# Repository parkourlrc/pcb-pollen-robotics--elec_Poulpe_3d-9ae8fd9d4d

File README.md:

# "Poulpe_3d" Electronic Board

"Poulpe_3d" is build from "Poulpe" as it aims on driving Orbita 3 Dofs. It is paireds with boards "Ventouse_3d" that drive 3 small BLDC Motors.

## Basically
 - Primarly designed for Reachy 2 gamma.
 - Powered in 24V.
 - Designed with KiCAD 7.

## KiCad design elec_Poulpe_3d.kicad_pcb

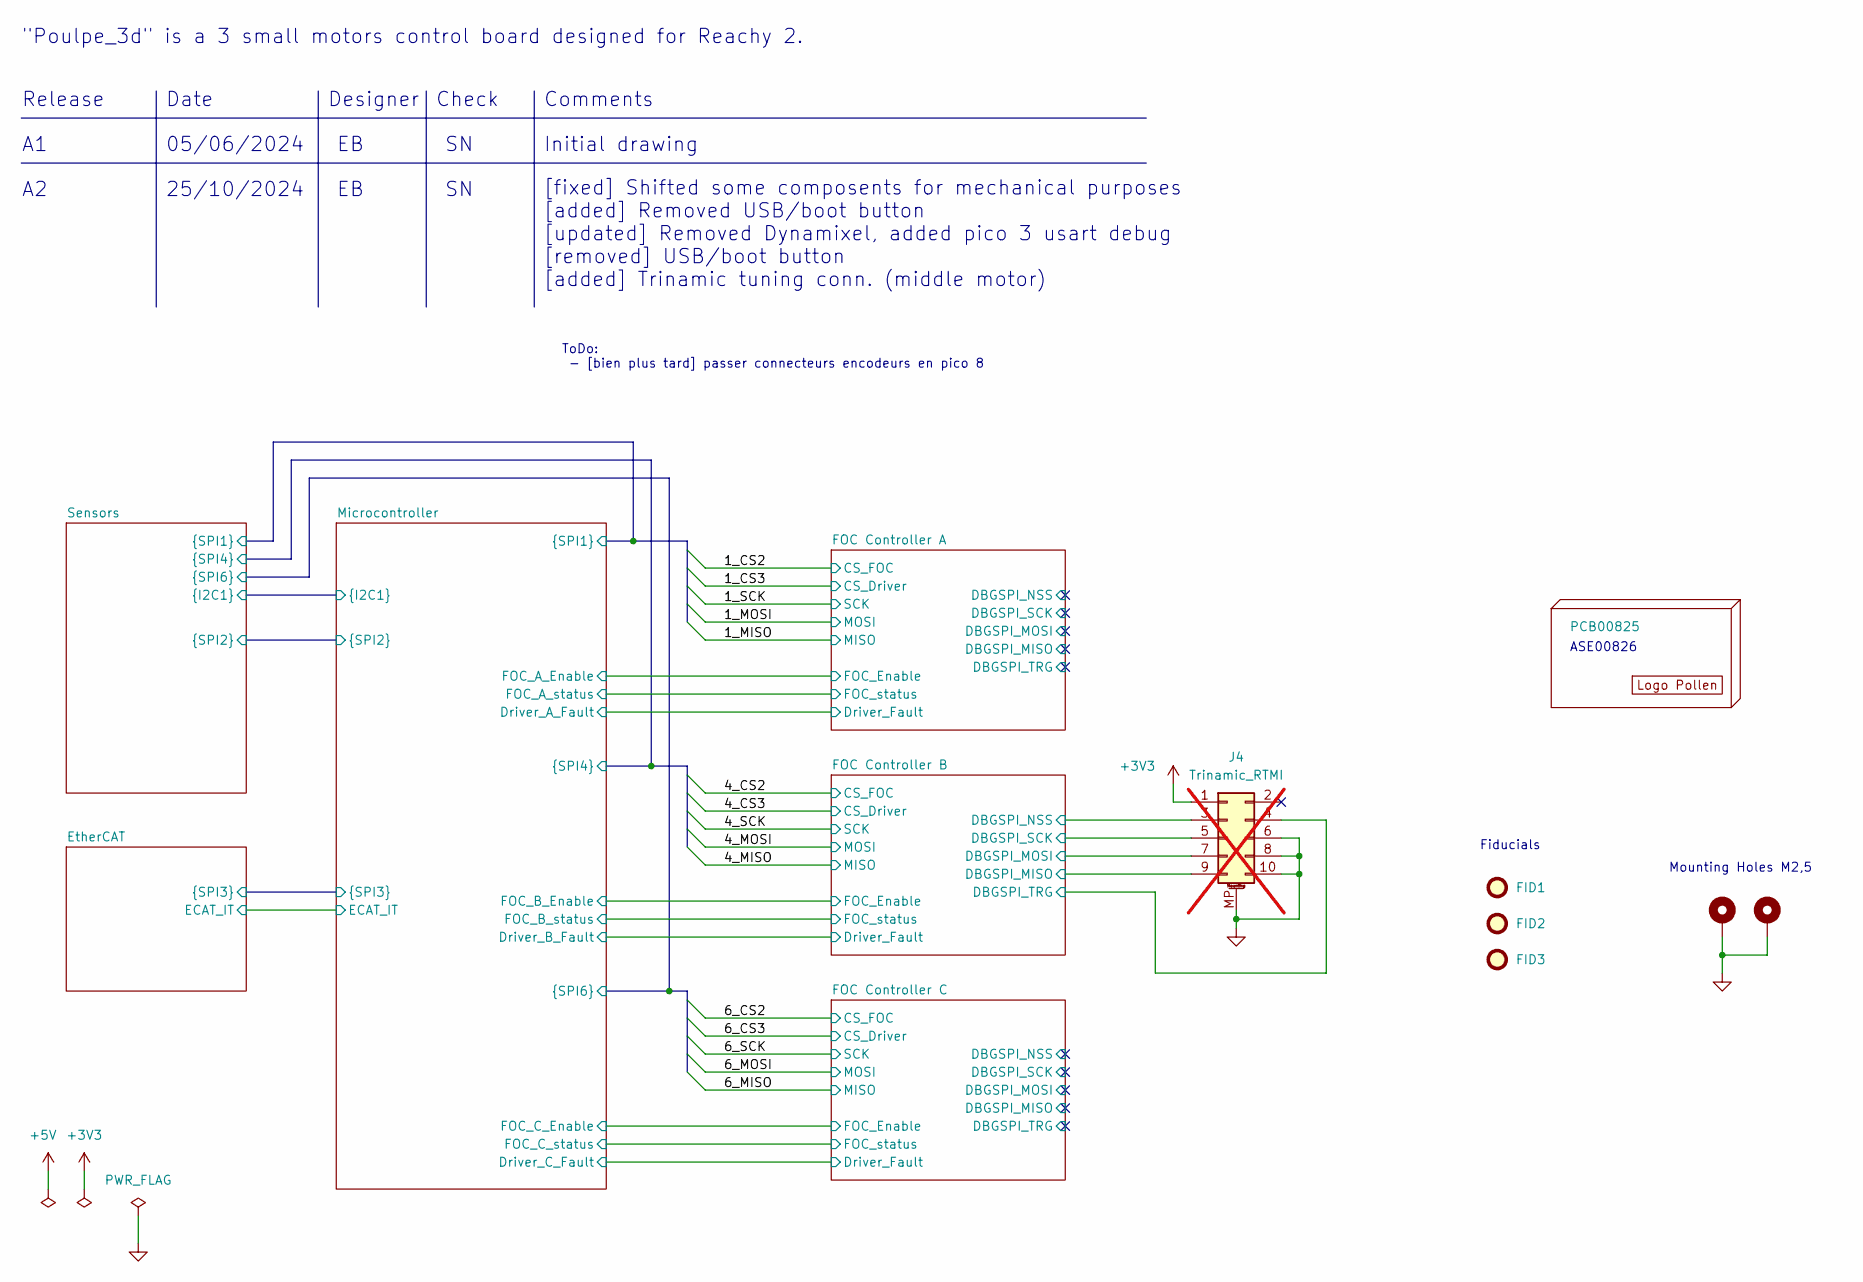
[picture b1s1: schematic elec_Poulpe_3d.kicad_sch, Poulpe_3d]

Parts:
FID1, FID2, FID3: DNP Fiducial; Fiducial_1mm_Mask2mm
H1: PCB00825
H2: DNP Logo Pollen 2021; Logo_Pollen_2021_sq
H3, H4: MountingHole_Pad; MountingHole_2.7mm_M2.5_ISO14580_Pad_TopBottom
J4: Trinamic_RTMI; DF20EF-10DP-1V (52); not fitted

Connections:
/FOC Controller B/DBGSPI_MISO: J4.9; also elsewhere on the board
/FOC Controller B/DBGSPI_MOSI: J4.7; also elsewhere on the board
/FOC Controller B/DBGSPI_NSS: J4.3; also elsewhere on the board
/FOC Controller B/DBGSPI_SCK: J4.5; also elsewhere on the board
/FOC Controller B/DBGSPI_TRG: J4.4; also elsewhere on the board

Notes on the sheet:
Mounting Holes M2,5
Date
Check
Release
Fiducials
ASE00826
Initial drawing
"Poulpe_3d" is a 3 small motors control board designed for Reachy 2.
Designer
25/10/2024
[fixed] Shifted some composents for mechanical purposes [added] Removed USB/boot button [updated] Removed Dynamixel, added pico 3 usart debug [removed] USB/boot button [added] Trinamic tuning conn. (middle motor)
Comments
ToDo: - [bien plus tard] passer connecteurs encodeurs en pico 8
05/06/2024

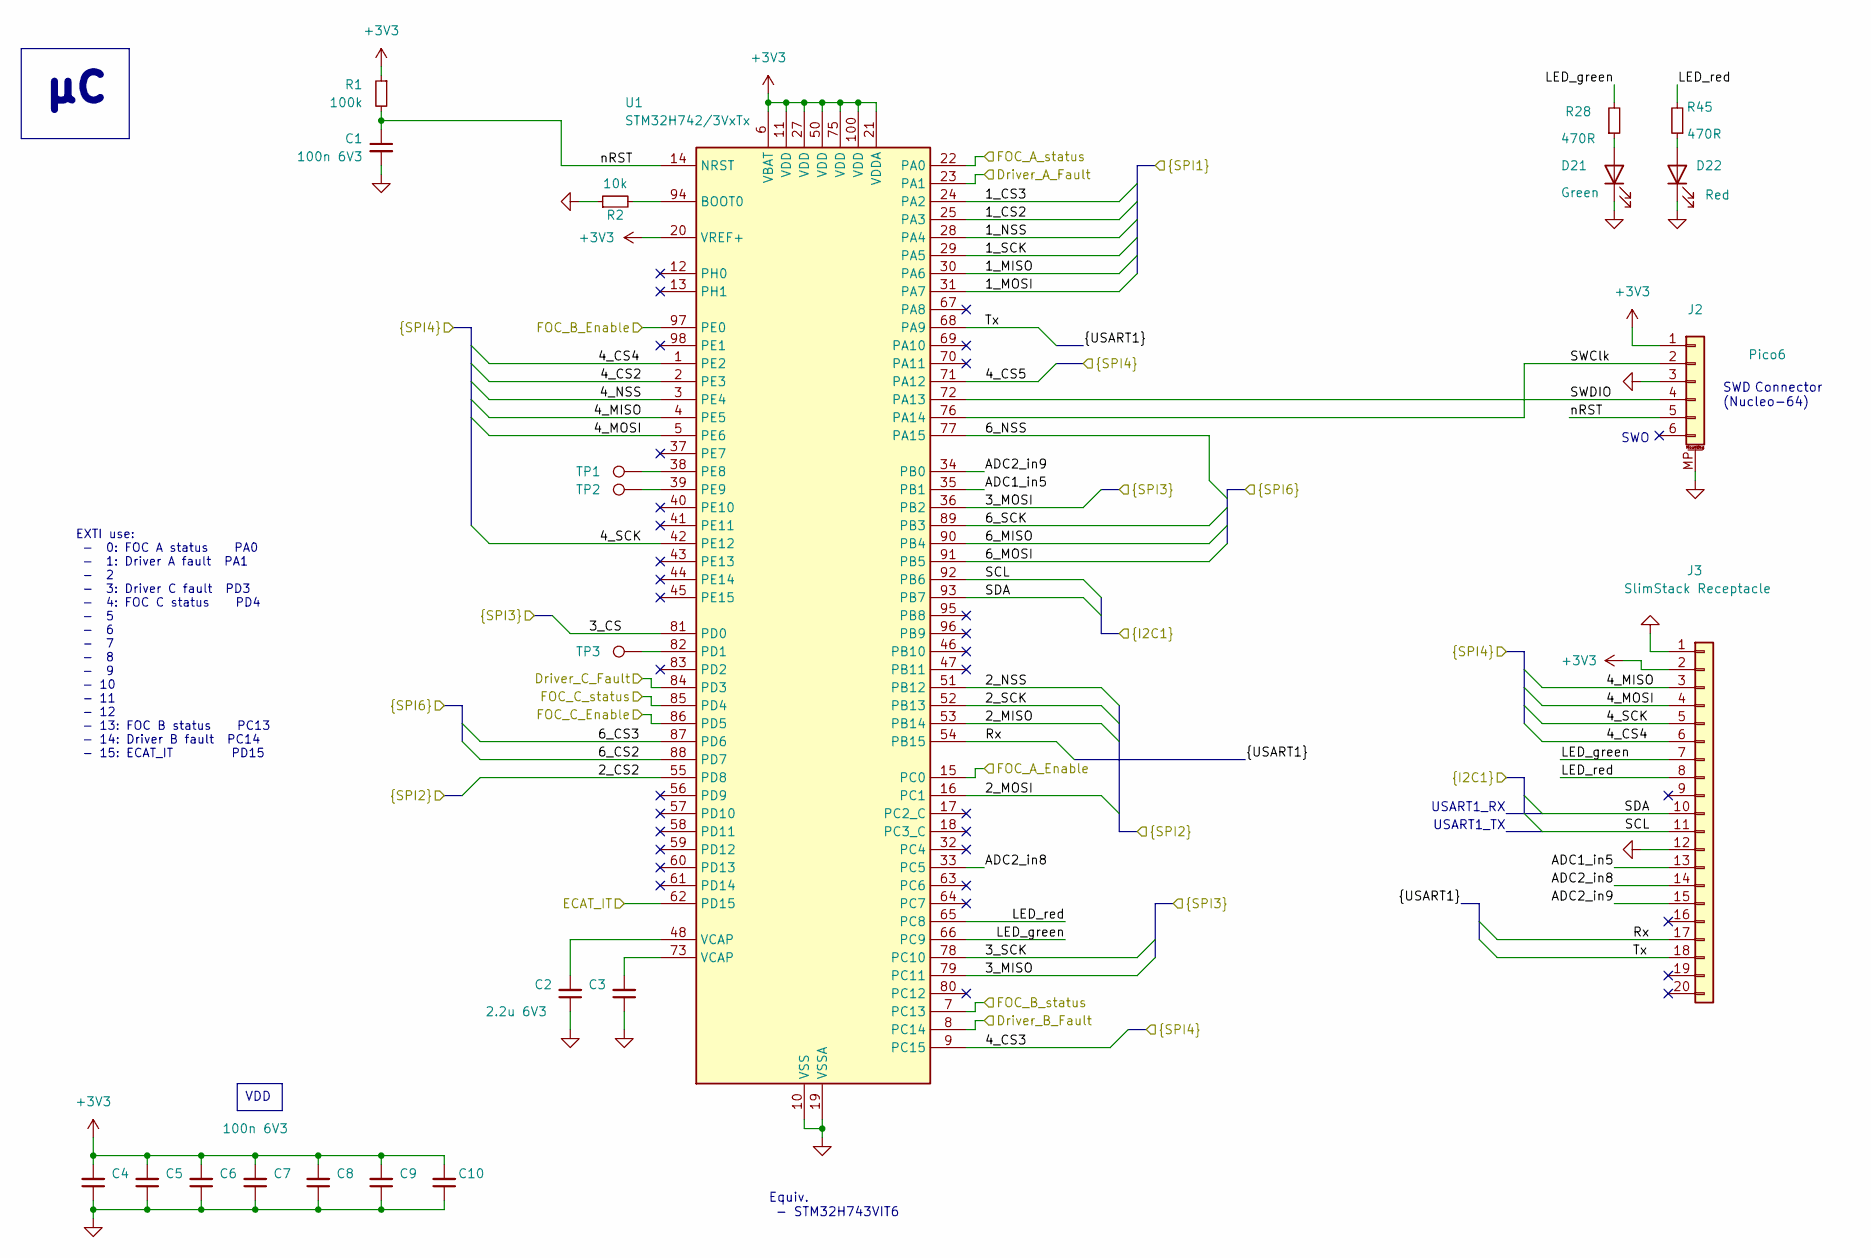
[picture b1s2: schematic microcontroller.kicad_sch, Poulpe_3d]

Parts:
C1, C4, C5, C6, C7, C8, C9, C10: 100n 6V3; C_0402_1005Metric
C2, C3: 2.2u 6V3; C_0603_1608Metric
D21: Green; LED_0603_1608Metric
D22: Red; LED_0603_1608Metric
J2: Pico6; Molex_PicoBlade_53261-0671_1x06-1MP_P1.25mm_Horizontal
J3: SlimStack Receptacle; Molex_SlimStack_529910208
R1: 100k; R_0402_1005Metric
R2: 10k; R_0402_1005Metric
R28, R45: 470R; R_0402_1005Metric
TP1, TP2, TP3: DNP - TestPoint; TestPoint_THTPad_D1.0mm_Drill0.4mm
U1: STM32H742/3VxTx; LQFP-100_14x14mm_P0.5mm

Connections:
/EtherCAT/3_CS: U1.81 (PD0); also elsewhere on the board
/EtherCAT/3_MISO: U1.79 (PC11); also elsewhere on the board
/EtherCAT/3_MOSI: U1.36 (PB2); also elsewhere on the board
/EtherCAT/3_SCK: U1.78 (PC10); also elsewhere on the board
/EtherCAT/ECAT_IT: U1.62 (PD15); also elsewhere on the board
/FOC Controller A/Driver_Fault: U1.23 (PA1); also elsewhere on the board
/FOC Controller A/FOC_Enable: U1.15 (PC0); also elsewhere on the board
/FOC Controller A/FOC_status: U1.22 (PA0); also elsewhere on the board
/FOC Controller B/Driver_Fault: U1.8 (PC14); also elsewhere on the board
/FOC Controller B/FOC_Enable: U1.97 (PE0); also elsewhere on the board
/FOC Controller B/FOC_status: U1.7 (PC13); also elsewhere on the board
/FOC Controller C/Driver_Fault: U1.84 (PD3); also elsewhere on the board
/FOC Controller C/FOC_Enable: U1.86 (PD5); also elsewhere on the board
/FOC Controller C/FOC_status: U1.85 (PD4); also elsewhere on the board
/Microcontroller/1_CS2: U1.25 (PA3); also elsewhere on the board
/Microcontroller/1_CS3: U1.24 (PA2); also elsewhere on the board
/Microcontroller/1_MISO: U1.30 (PA6); also elsewhere on the board
/Microcontroller/1_MOSI: U1.31 (PA7); also elsewhere on the board
/Microcontroller/1_NSS: U1.28 (PA4); also elsewhere on the board
/Microcontroller/1_SCK: U1.29 (PA5); also elsewhere on the board
/Microcontroller/2_CS2: U1.55 (PD8); also elsewhere on the board
/Microcontroller/2_MISO: U1.53 (PB14); also elsewhere on the board
/Microcontroller/2_MOSI: U1.16 (PC1); also elsewhere on the board
/Microcontroller/2_NSS: U1.51 (PB12); also elsewhere on the board
/Microcontroller/2_SCK: U1.52 (PB13); also elsewhere on the board
/Microcontroller/4_CS2: U1.2 (PE3); also elsewhere on the board
/Microcontroller/4_CS3: U1.9 (PC15); also elsewhere on the board
/Microcontroller/4_CS4: J3.6, U1.1 (PE2)
/Microcontroller/4_CS5: U1.71 (PA12); also elsewhere on the board
/Microcontroller/4_MISO: J3.3, U1.4 (PE5); also elsewhere on the board
/Microcontroller/4_MOSI: J3.4, U1.5 (PE6); also elsewhere on the board
/Microcontroller/4_NSS: U1.3 (PE4); also elsewhere on the board
/Microcontroller/4_SCK: J3.5, U1.42 (PE12); also elsewhere on the board
/Microcontroller/6_CS2: U1.88 (PD7); also elsewhere on the board
/Microcontroller/6_CS3: U1.87 (PD6); also elsewhere on the board
/Microcontroller/6_MISO: U1.90 (PB4); also elsewhere on the board
/Microcontroller/6_MOSI: U1.91 (PB5); also elsewhere on the board
/Microcontroller/6_NSS: U1.77 (PA15); also elsewhere on the board
/Microcontroller/6_SCK: U1.89 (PB3); also elsewhere on the board
/Microcontroller/ADC1_in5: J3.13, U1.35 (PB1)
/Microcontroller/ADC2_in8: J3.14, U1.33 (PC5)
/Microcontroller/ADC2_in9: J3.15, U1.34 (PB0)
/Microcontroller/LED_green: J3.7, R28.2, U1.66 (PC9)
/Microcontroller/LED_red: J3.8, R45.2, U1.65 (PC8)
/Microcontroller/Rx: J3.17, U1.54 (PB15)
/Microcontroller/SCL: J3.11, U1.92 (PB6); also elsewhere on the board
/Microcontroller/SDA: J3.10, U1.93 (PB7); also elsewhere on the board
/Microcontroller/SWClk: J2.2, U1.76 (PA14)
/Microcontroller/SWDIO: J2.4, U1.72 (PA13)
/Microcontroller/Tx: J3.18, U1.68 (PA9)
/Microcontroller/nRST: C1.1, J2.5, R1.2, U1.14 (NRST)
unnamed: C2.2, U1.48 (VCAP)
unnamed: C3.2, U1.73 (VCAP)
unnamed: D21.2 (A), R28.1
unnamed: D22.2 (A), R45.1
unnamed: R2.2, U1.94 (BOOT0)
unnamed: TP3.1, U1.82 (PD1)
unnamed: TP1.1, U1.38 (PE8)
unnamed: TP2.1, U1.39 (PE9)

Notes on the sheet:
VDD
SWO
USART1_RX
USART1_TX
EXTI use: - 0: FOC A status PA0 - 1: Driver A fault PA1 - 2 - 3: Driver C fault PD3 - 4: FOC C status PD4 - 5 - 6 - 7 - 8 - 9 - 10 - 11 - 12 - 13: FOC B status PC13 - 14: Driver B fault PC14 - 15: ECAT_IT PD15
Equiv. - STM32H743VIT6
SWD Connector (Nucleo-64)

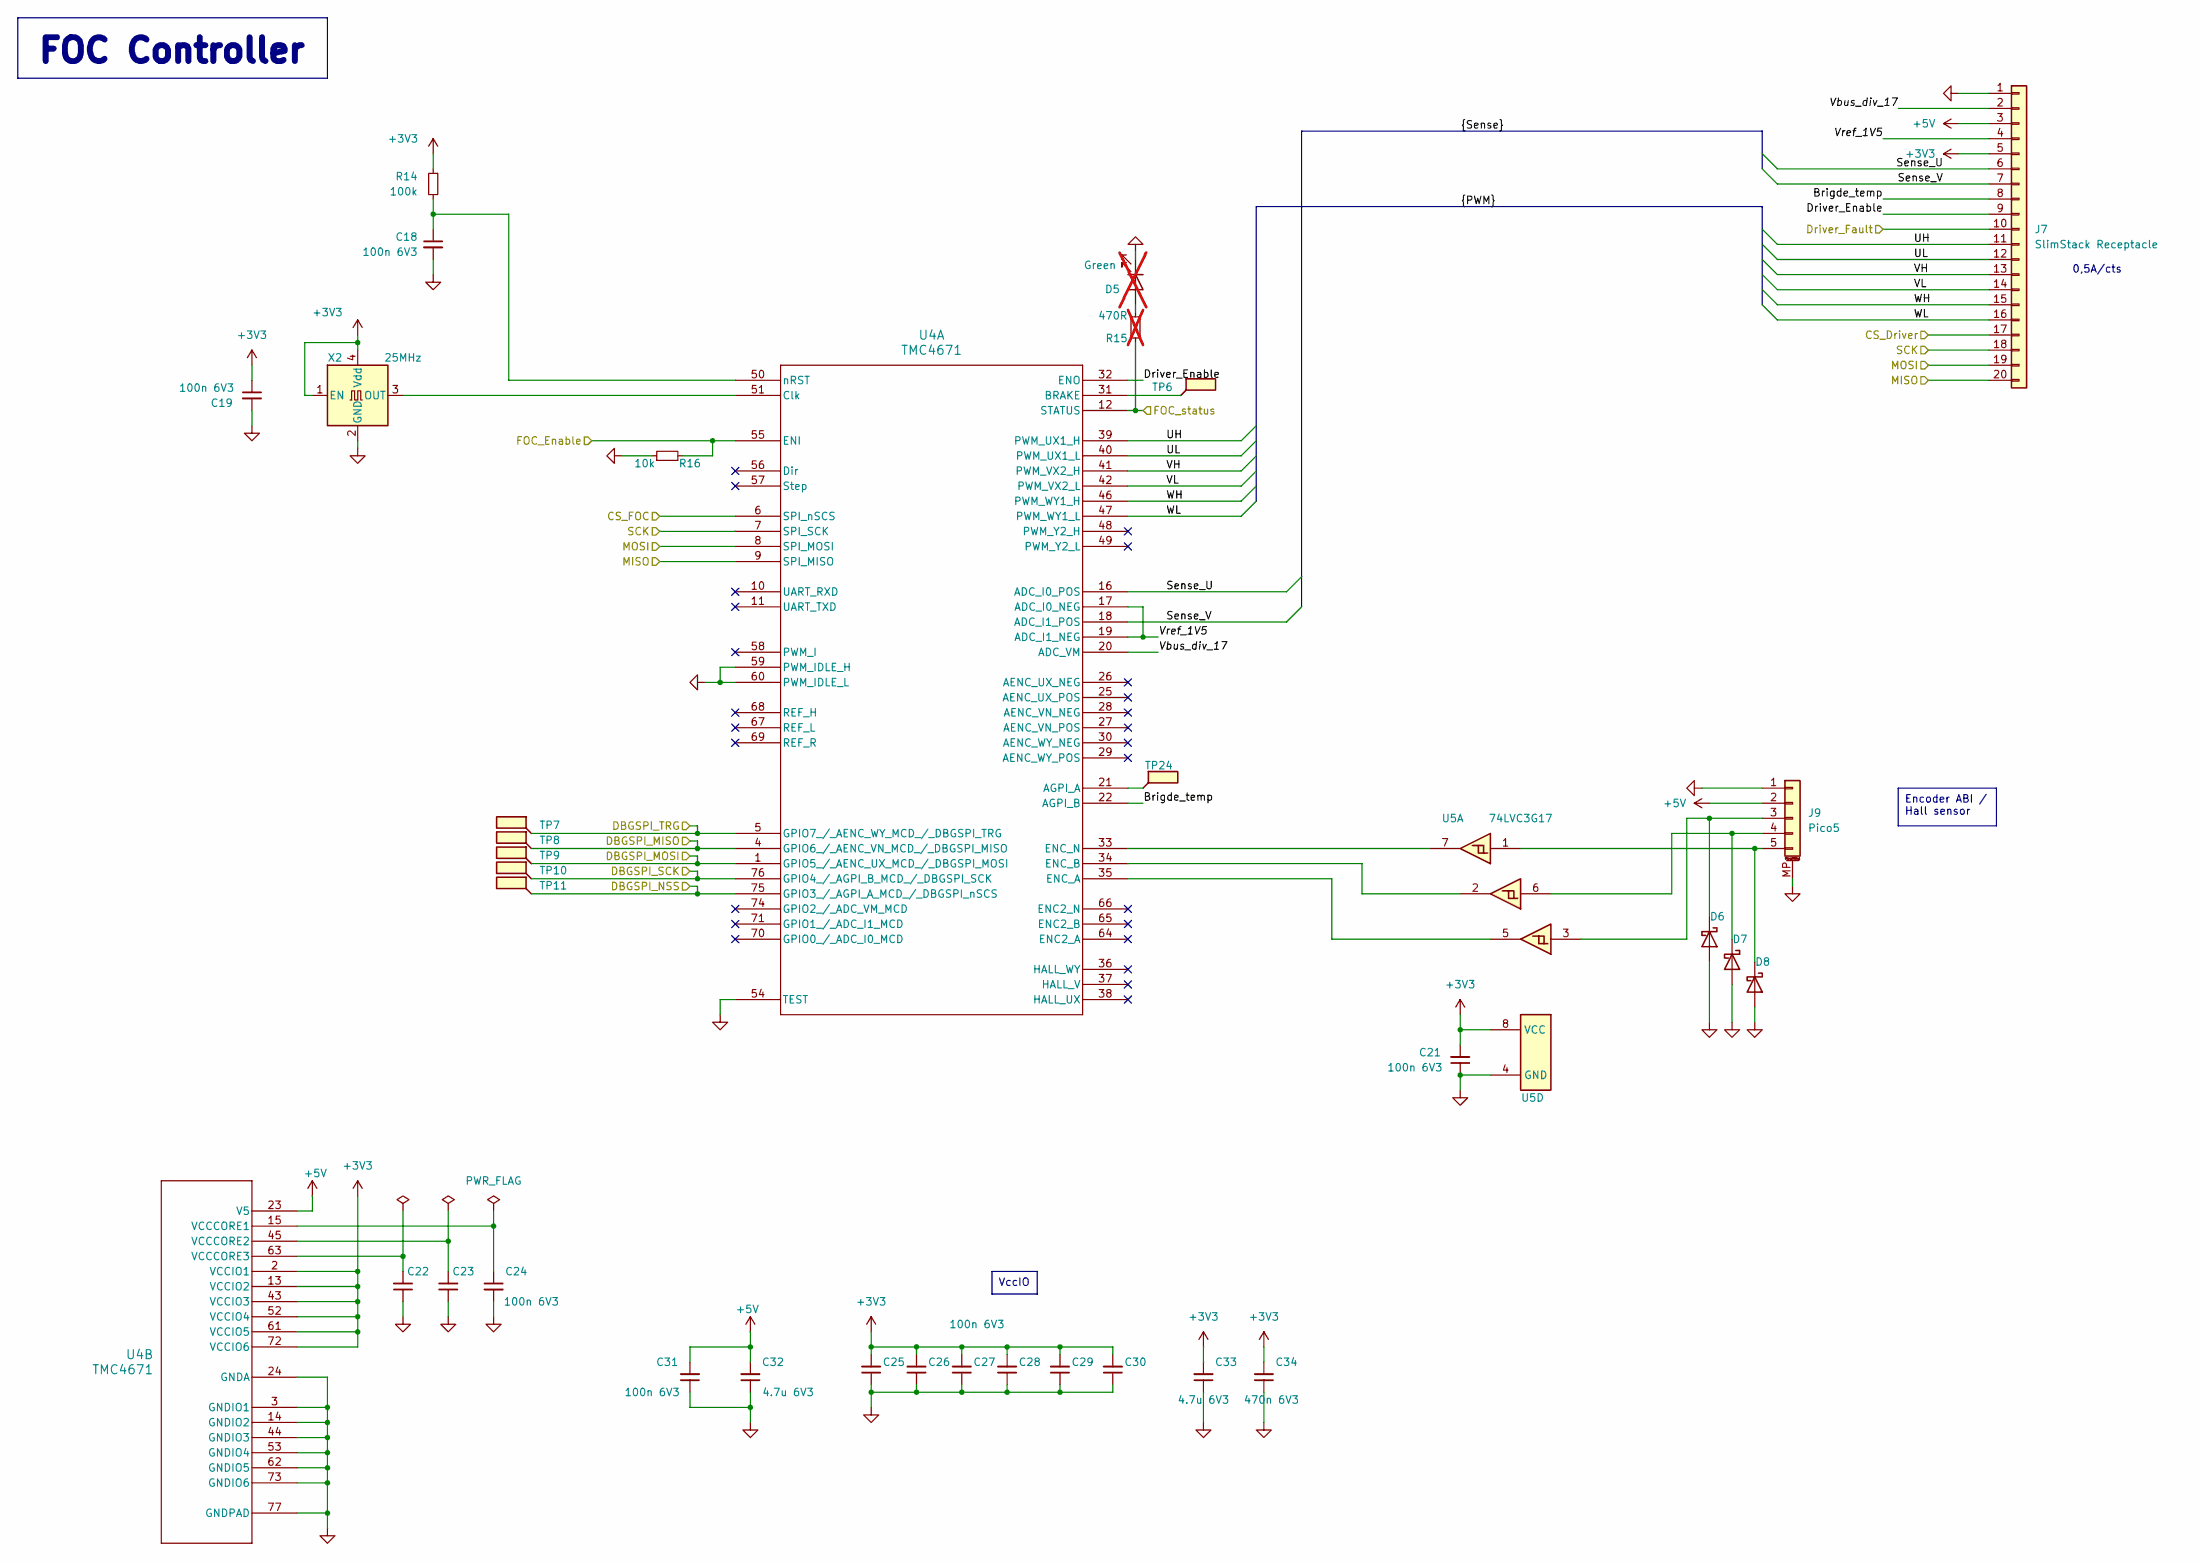
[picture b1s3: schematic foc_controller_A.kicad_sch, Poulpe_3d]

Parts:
C18, C19, C21, C22, C23, C24, C25, C26, C27, C28, C29, C30, C31: 100n 6V3; C_0402_1005Metric
C32, C33: 4.7u 6V3; C_0402_1005Metric
C34: 470n 6V3; C_0402_1005Metric
D5: Green; LED_0603_1608Metric; not fitted
D6, D7, D8: D_Schottky; D_SOD-323
J7: SlimStack Receptacle; Molex_SlimStack_529910208
J9: Pico5; Molex_PicoBlade_53261-0571_1x05-1MP_P1.25mm_Horizontal
R14: 100k; R_0402_1005Metric
R15: 470R; R_0402_1005Metric; not fitted
R16: 10k; R_0402_1005Metric
TP6, TP7, TP8, TP9, TP10, TP11, TP24: TestPoint_Flag; TestPoint_Line_0.2x0.8mm
U4: TMC4671; QFN76_11P5X6P5_TRI
U5: 74LVC3G17; VSSOP-8_2.4x2.1mm_P0.5mm
X2: 25MHz; Abracon_ASE-4Pin_3.2x2.5mm

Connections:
/FOC Controller A/Brigde_temp: J7.8, U4.22 (AGPI_B)
/FOC Controller A/DBGSPI_MISO: TP8.1, U4.4 (GPIO6_/_AENC_VN_MCD_/_DBGSPI_MISO)
/FOC Controller A/DBGSPI_MOSI: TP9.1, U4.1 (GPIO5_/_AENC_UX_MCD_/_DBGSPI_MOSI)
/FOC Controller A/DBGSPI_NSS: TP11.1, U4.75 (GPIO3_/_AGPI_A_MCD_/_DBGSPI_nSCS)
/FOC Controller A/DBGSPI_SCK: TP10.1, U4.76 (GPIO4_/_AGPI_B_MCD_/_DBGSPI_SCK)
/FOC Controller A/DBGSPI_TRG: TP7.1, U4.5 (GPIO7_/_AENC_WY_MCD_/_DBGSPI_TRG)
/FOC Controller A/Driver_Enable: J7.9, U4.32 (ENO)
/FOC Controller A/Driver_Fault: J7.10; also elsewhere on the board
/FOC Controller A/FOC_Enable: R16.2, U4.55 (ENI); also elsewhere on the board
/FOC Controller A/FOC_status: R15.2, U4.12 (STATUS); also elsewhere on the board
/FOC Controller A/Sense_U: J7.6, U4.16 (ADC_I0_POS)
/FOC Controller A/Sense_V: J7.7, U4.18 (ADC_I1_POS)
/FOC Controller A/UH: J7.11, U4.39 (PWM_UX1_H)
/FOC Controller A/UL: J7.12, U4.40 (PWM_UX1_L)
/FOC Controller A/VH: J7.13, U4.41 (PWM_VX2_H)
/FOC Controller A/VL: J7.14, U4.42 (PWM_VX2_L)
/FOC Controller A/Vbus_div_17: J7.2, U4.20 (ADC_VM)
/FOC Controller A/Vref_1V5: J7.4, U4.17 (ADC_I0_NEG), U4.19 (ADC_I1_NEG)
/FOC Controller A/WH: J7.15, U4.46 (PWM_WY1_H)
/FOC Controller A/WL: J7.16, U4.47 (PWM_WY1_L)
/Microcontroller/1_CS2: U4.6 (SPI_nSCS); also elsewhere on the board
/Microcontroller/1_CS3: J7.17; also elsewhere on the board
/Microcontroller/1_MISO: J7.20, U4.9 (SPI_MISO); also elsewhere on the board
/Microcontroller/1_MOSI: J7.19, U4.8 (SPI_MOSI); also elsewhere on the board
/Microcontroller/1_SCK: J7.18, U4.7 (SPI_SCK); also elsewhere on the board
unnamed: D5.2 (A), R15.1
unnamed: D6.1 (K), J9.3, U5.3
unnamed: D7.1 (K), J9.4, U5.6
unnamed: D8.1 (K), J9.5, U5.1
unnamed: TP24.1, U4.21 (AGPI_A)
unnamed: TP6.1, U4.31 (BRAKE)
unnamed: U4.51 (Clk), X2.3 (OUT)
unnamed: U4.35 (ENC_A), U5.5
unnamed: U4.34 (ENC_B), U5.2
unnamed: U4.33 (ENC_N), U5.7
unnamed: C18.1, R14.2, U4.50 (nRST)
unnamed: C24.1, U4.15 (VCCCORE1)
unnamed: C23.2, U4.45 (VCCCORE2)
unnamed: C22.2, U4.63 (VCCCORE3)

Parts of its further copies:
C20, C35, C36, C37, C38, C39, C42, C43, C44, C45, C46, C49, C50, C51, C52, C53, C54, C55, C57, C58, C59, C60, C61, C62, C65: 100n 6V3; C_0402_1005Metric
C47, C56, C63: 4.7u 6V3; C_0402_1005Metric
C48, C64: 470n 6V3; C_0402_1005Metric
D9, D13: Green; LED_0603_1608Metric; not fitted
D10, D11, D12, D14, D15, D16: D_Schottky; D_SOD-323
J10, J12: Pico5; Molex_PicoBlade_53261-0571_1x05-1MP_P1.25mm_Horizontal
J11, J13: SlimStack Receptacle; Molex_SlimStack_529910208
R17, R20: 100k; R_0402_1005Metric
R18, R21: 10k; R_0402_1005Metric
R19, R22: 470R; R_0402_1005Metric; not fitted
TP12, TP13, TP14, TP15, TP16, TP17, TP18, TP19, TP20, TP21, TP22, TP23, TP25, TP26: TestPoint_Flag; TestPoint_Line_0.2x0.8mm
U6, U8: TMC4671; QFN76_11P5X6P5_TRI
U7, U9: 74LVC3G17; VSSOP-8_2.4x2.1mm_P0.5mm
X3, X4: 25MHz; Abracon_ASE-4Pin_3.2x2.5mm

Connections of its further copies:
/FOC Controller B/Brigde_temp: J11.8, U6.22 (AGPI_B)
/FOC Controller B/DBGSPI_MISO: TP13.1, U6.4 (GPIO6_/_AENC_VN_MCD_/_DBGSPI_MISO); also elsewhere on the board
/FOC Controller B/DBGSPI_MOSI: TP14.1, U6.1 (GPIO5_/_AENC_UX_MCD_/_DBGSPI_MOSI); also elsewhere on the board
/FOC Controller B/DBGSPI_NSS: TP16.1, U6.75 (GPIO3_/_AGPI_A_MCD_/_DBGSPI_nSCS); also elsewhere on the board
/FOC Controller B/DBGSPI_SCK: TP15.1, U6.76 (GPIO4_/_AGPI_B_MCD_/_DBGSPI_SCK); also elsewhere on the board
/FOC Controller B/DBGSPI_TRG: TP12.1, U6.5 (GPIO7_/_AENC_WY_MCD_/_DBGSPI_TRG); also elsewhere on the board
/FOC Controller B/Driver_Enable: J11.9, U6.32 (ENO)
/FOC Controller B/Driver_Fault: J11.10; also elsewhere on the board
/FOC Controller B/FOC_Enable: R18.2, U6.55 (ENI); also elsewhere on the board
/FOC Controller B/FOC_status: R19.2, U6.12 (STATUS); also elsewhere on the board
/FOC Controller B/Sense_U: J11.6, U6.16 (ADC_I0_POS)
/FOC Controller B/Sense_V: J11.7, U6.18 (ADC_I1_POS)
/FOC Controller B/UH: J11.11, U6.39 (PWM_UX1_H)
/FOC Controller B/UL: J11.12, U6.40 (PWM_UX1_L)
/FOC Controller B/VH: J11.13, U6.41 (PWM_VX2_H)
/FOC Controller B/VL: J11.14, U6.42 (PWM_VX2_L)
/FOC Controller B/Vbus_div_17: J11.2, U6.20 (ADC_VM)
/FOC Controller B/Vref_1V5: J11.4, U6.17 (ADC_I0_NEG), U6.19 (ADC_I1_NEG)
/FOC Controller B/WH: J11.15, U6.46 (PWM_WY1_H)
/FOC Controller B/WL: J11.16, U6.47 (PWM_WY1_L)
/FOC Controller C/Brigde_temp: J13.8, U8.22 (AGPI_B)
/FOC Controller C/DBGSPI_MISO: TP20.1, U8.4 (GPIO6_/_AENC_VN_MCD_/_DBGSPI_MISO)
/FOC Controller C/DBGSPI_MOSI: TP21.1, U8.1 (GPIO5_/_AENC_UX_MCD_/_DBGSPI_MOSI)
/FOC Controller C/DBGSPI_NSS: TP23.1, U8.75 (GPIO3_/_AGPI_A_MCD_/_DBGSPI_nSCS)
/FOC Controller C/DBGSPI_SCK: TP22.1, U8.76 (GPIO4_/_AGPI_B_MCD_/_DBGSPI_SCK)
/FOC Controller C/DBGSPI_TRG: TP19.1, U8.5 (GPIO7_/_AENC_WY_MCD_/_DBGSPI_TRG)
/FOC Controller C/Driver_Enable: J13.9, U8.32 (ENO)
/FOC Controller C/Driver_Fault: J13.10; also elsewhere on the board
/FOC Controller C/FOC_Enable: R21.2, U8.55 (ENI); also elsewhere on the board
/FOC Controller C/FOC_status: R22.2, U8.12 (STATUS); also elsewhere on the board
/FOC Controller C/Sense_U: J13.6, U8.16 (ADC_I0_POS)
/FOC Controller C/Sense_V: J13.7, U8.18 (ADC_I1_POS)
/FOC Controller C/UH: J13.11, U8.39 (PWM_UX1_H)
/FOC Controller C/UL: J13.12, U8.40 (PWM_UX1_L)
/FOC Controller C/VH: J13.13, U8.41 (PWM_VX2_H)
/FOC Controller C/VL: J13.14, U8.42 (PWM_VX2_L)
/FOC Controller C/Vbus_div_17: J13.2, U8.20 (ADC_VM)
/FOC Controller C/Vref_1V5: J13.4, U8.17 (ADC_I0_NEG), U8.19 (ADC_I1_NEG)
/FOC Controller C/WH: J13.15, U8.46 (PWM_WY1_H)
/FOC Controller C/WL: J13.16, U8.47 (PWM_WY1_L)
/Microcontroller/4_CS2: U6.6 (SPI_nSCS); also elsewhere on the board
/Microcontroller/4_CS3: J11.17; also elsewhere on the board
/Microcontroller/4_MISO: J11.20, U6.9 (SPI_MISO); also elsewhere on the board
/Microcontroller/4_MOSI: J11.19, U6.8 (SPI_MOSI); also elsewhere on the board
/Microcontroller/4_SCK: J11.18, U6.7 (SPI_SCK); also elsewhere on the board
/Microcontroller/6_CS2: U8.6 (SPI_nSCS); also elsewhere on the board
/Microcontroller/6_CS3: J13.17; also elsewhere on the board
/Microcontroller/6_MISO: J13.20, U8.9 (SPI_MISO); also elsewhere on the board
/Microcontroller/6_MOSI: J13.19, U8.8 (SPI_MOSI); also elsewhere on the board
/Microcontroller/6_SCK: J13.18, U8.7 (SPI_SCK); also elsewhere on the board
unnamed: D9.2 (A), R19.1
unnamed: D10.1 (K), J10.3, U7.3
unnamed: D11.1 (K), J10.4, U7.6
unnamed: D12.1 (K), J10.5, U7.1
unnamed: D13.2 (A), R22.1
unnamed: D14.1 (K), J12.3, U9.3
unnamed: D15.1 (K), J12.4, U9.6
unnamed: D16.1 (K), J12.5, U9.1
unnamed: TP17.1, U6.21 (AGPI_A)
unnamed: TP18.1, U6.31 (BRAKE)
unnamed: U6.51 (Clk), X3.3 (OUT)
unnamed: U6.35 (ENC_A), U7.5
unnamed: U6.34 (ENC_B), U7.2
unnamed: U6.33 (ENC_N), U7.7
unnamed: C36.1, R17.2, U6.50 (nRST)
unnamed: C38.1, U6.15 (VCCCORE1)
unnamed: C37.2, U6.45 (VCCCORE2)
unnamed: C35.2, U6.63 (VCCCORE3)
unnamed: TP25.1, U8.21 (AGPI_A)
unnamed: TP26.1, U8.31 (BRAKE)
unnamed: U8.51 (Clk), X4.3 (OUT)
unnamed: U8.35 (ENC_A), U9.5
unnamed: U8.34 (ENC_B), U9.2
unnamed: U8.33 (ENC_N), U9.7
unnamed: C52.1, R20.2, U8.50 (nRST)
unnamed: C54.1, U8.15 (VCCCORE1)
unnamed: C53.2, U8.45 (VCCCORE2)
unnamed: C51.2, U8.63 (VCCCORE3)

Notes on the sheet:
Encoder ABI / Hall sensor
FOC Controller
VccIO
0,5A/cts

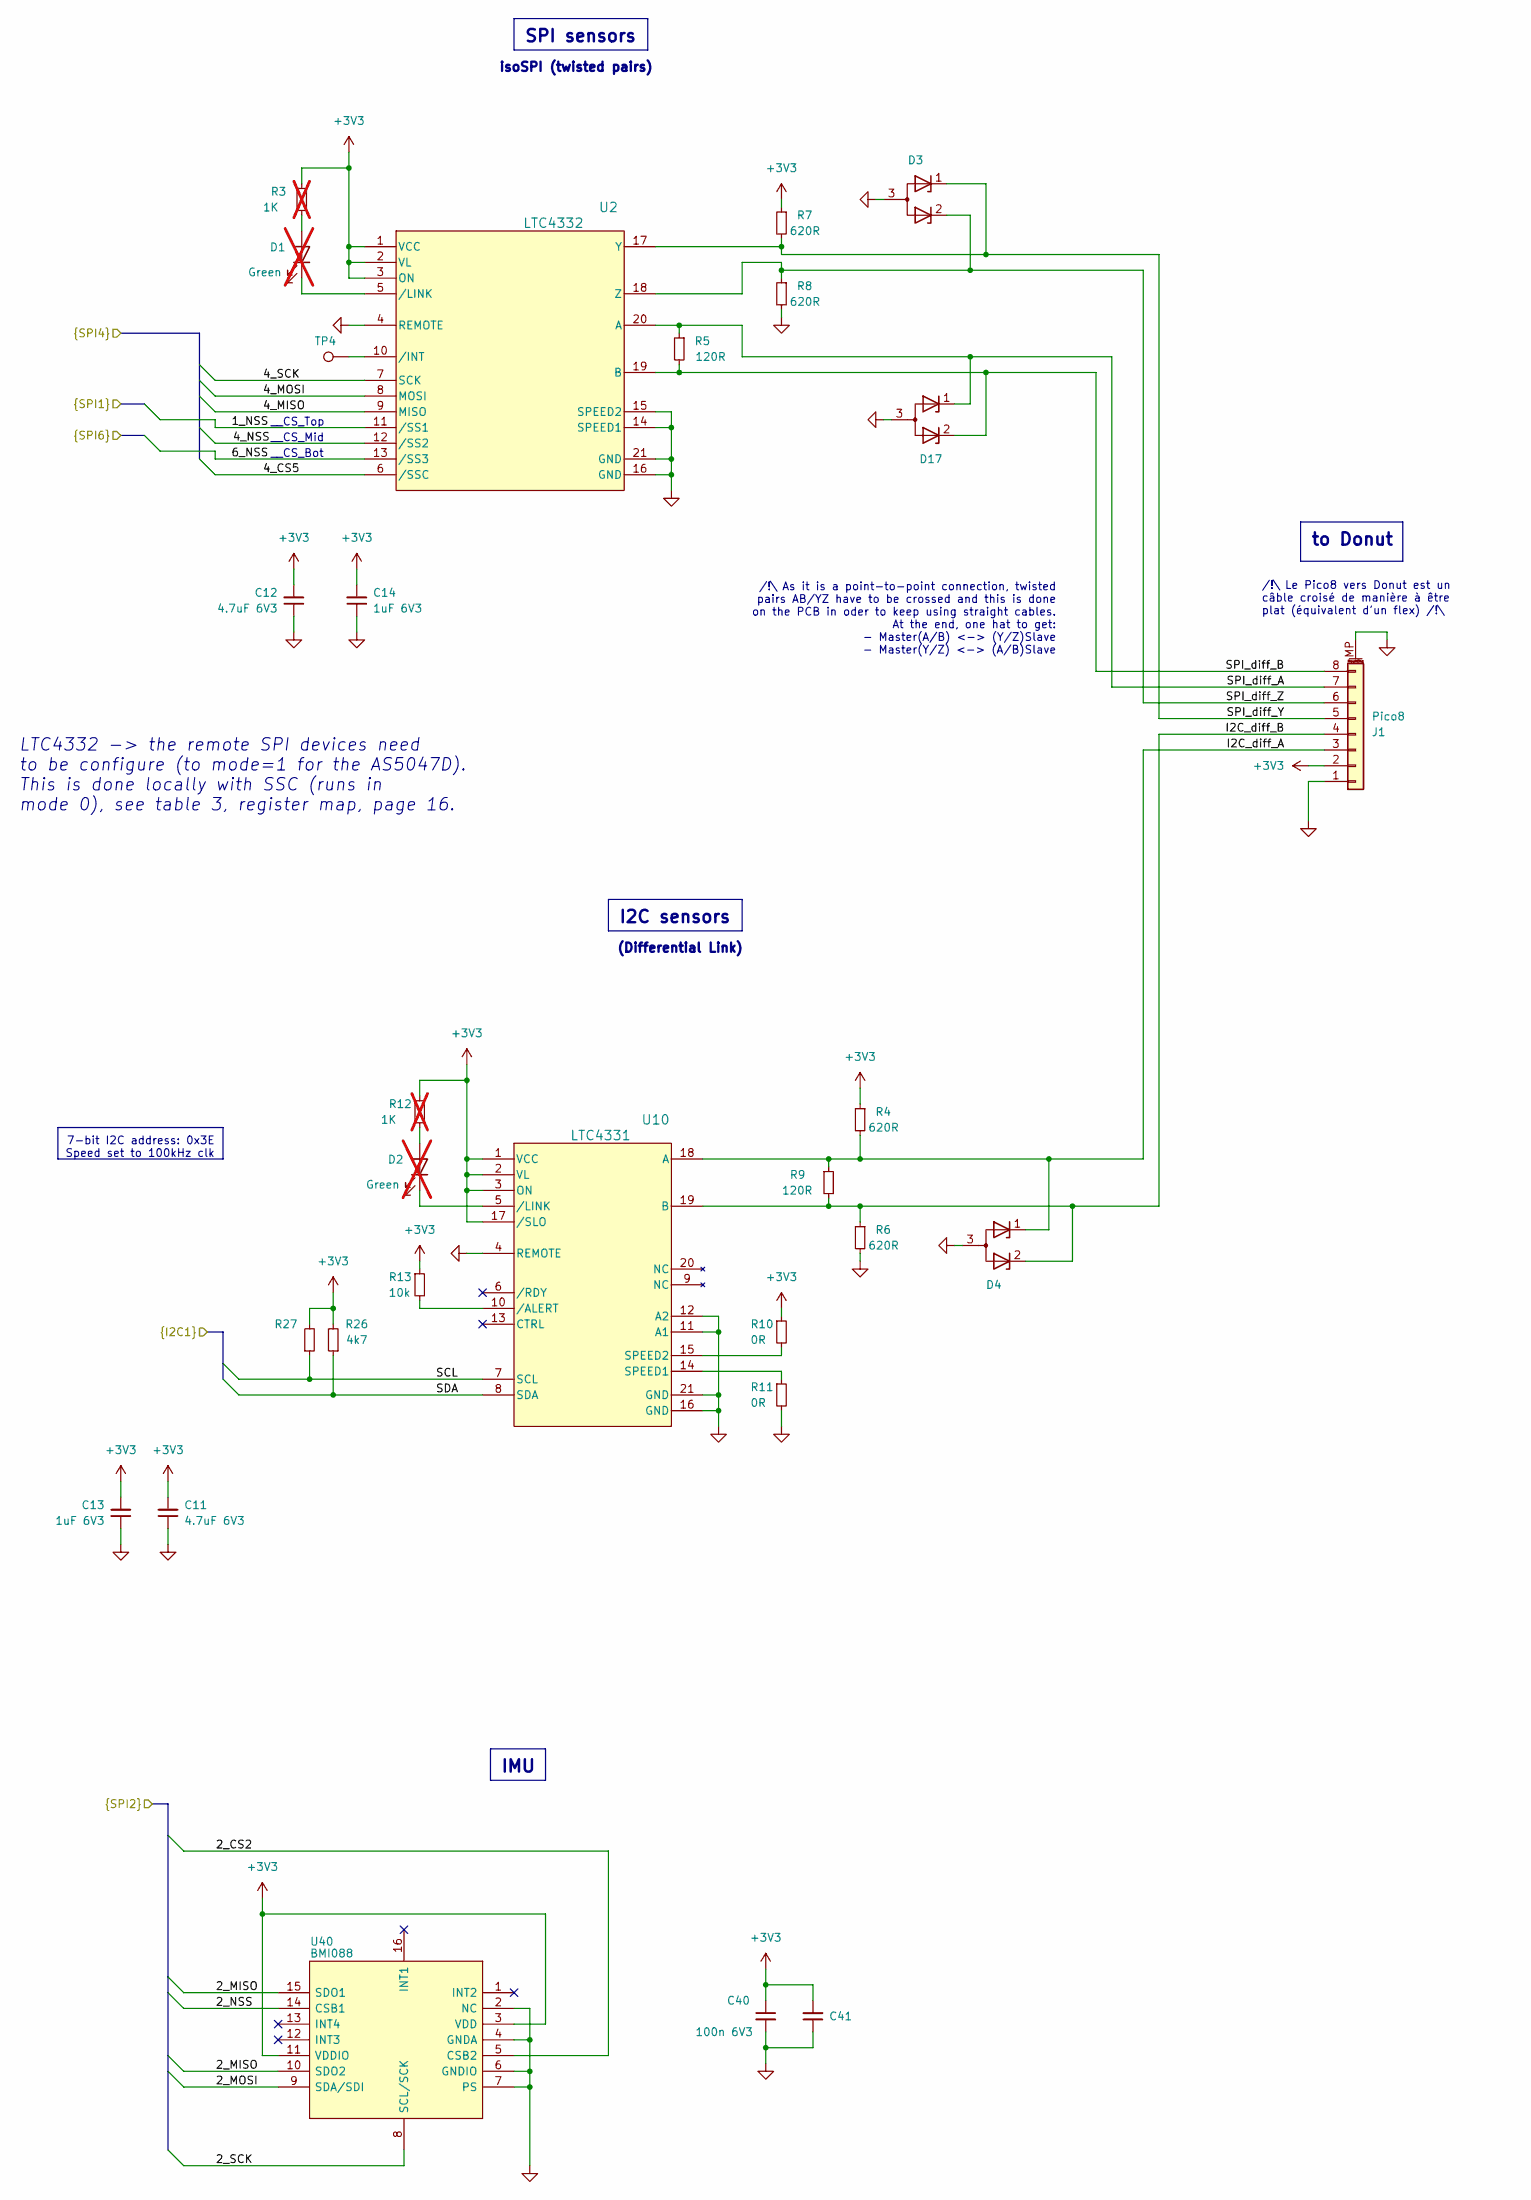
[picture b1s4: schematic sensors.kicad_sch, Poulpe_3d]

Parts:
C11, C12: 4.7uF 6V3; C_0402_1005Metric
C13, C14: 1uF 6V3; C_0402_1005Metric
C40, C41: 100n 6V3; C_0402_1005Metric
D1, D2: Green; LED_0603_1608Metric; not fitted
D3, D4, D17: Dual TVS Diode; SOT-23
J1: Pico8; Molex_PicoBlade_53261-0871_1x08-1MP_P1.25mm_Horizontal
R3, R12: 1K; R_0603_1608Metric; not fitted
R4, R6, R7, R8: 620R; R_0402_1005Metric
R5, R9: 120R; R_0402_1005Metric
R10, R11: 0R; R_0402_1005Metric
R13: 10k; R_0402_1005Metric
R26, R27: 4k7; R_0402_1005Metric
TP4: TestPoint; TestPoint_Pad_D1.0mm
U2: LTC4332; LPQFN20_ADI
U10: LTC4331; LPQFN20_ADI
U40: BMI088

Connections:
/Microcontroller/1_NSS: U2.11 (/SS1); also elsewhere on the board
/Microcontroller/4_CS5: U2.6 (/SSC); also elsewhere on the board
/Microcontroller/4_MISO: U2.9 (MISO); also elsewhere on the board
/Microcontroller/4_MOSI: U2.8 (MOSI); also elsewhere on the board
/Microcontroller/4_NSS: U2.12 (/SS2); also elsewhere on the board
/Microcontroller/4_SCK: U2.7 (SCK); also elsewhere on the board
/Microcontroller/6_NSS: U2.13 (/SS3); also elsewhere on the board
/Microcontroller/SCL: R27.1, U10.7 (SCL); also elsewhere on the board
/Microcontroller/SDA: R26.1, U10.8 (SDA); also elsewhere on the board
/Sensors/I2C_diff_A: D4.1 (K), J1.3, R4.2, R9.1, U10.18 (A)
/Sensors/I2C_diff_B: D4.2 (K), J1.4, R6.1, R9.2, U10.19 (B)
/Sensors/SPI_diff_A: D17.1 (K), J1.7, R5.1, U2.20 (A)
/Sensors/SPI_diff_B: D17.2 (K), J1.8, R5.2, U2.19 (B)
/Sensors/SPI_diff_Y: D3.1 (K), J1.5, R7.2, U2.17 (Y)
/Sensors/SPI_diff_Z: D3.2 (K), J1.6, R8.1, U2.18 (Z)
unnamed: D1.2 (A), R3.2
unnamed: D1.1 (K), U2.5 (/LINK)
unnamed: D2.2 (A), R12.2
unnamed: D2.1 (K), U10.5 (/LINK)
unnamed: TP4.1, U2.10 (/INT)
unnamed: R11.1, U10.14 (SPEED1)
unnamed: R10.2, U10.15 (SPEED2)
unnamed: R13.2, U10.10 (/ALERT)

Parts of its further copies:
C16, C17: 100n 6V3; C_0402_1005Metric
U3: BMI088

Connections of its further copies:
/Microcontroller/2_CS2: U3.5 (CSB2); also elsewhere on the board
/Microcontroller/2_MISO: U3.10 (SDO2), U3.15 (SDO1); also elsewhere on the board
/Microcontroller/2_MOSI: U3.9 (SDA/SDI); also elsewhere on the board
/Microcontroller/2_NSS: U3.14 (CSB1); also elsewhere on the board
/Microcontroller/2_SCK: U3.8 (SCL/SCK); also elsewhere on the board

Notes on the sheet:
SPI sensors
IMU
I2C sensors
to Donut
/!\ As it is a point-to-point connection, twisted pairs AB/YZ have to be crossed and this is done on the PCB in oder to keep using straight cables. At the end, one hat to get: - Master(A/B) <-> (Y/Z)Slave - Master(Y/Z) <-> (A/B)Slave
(Differential Link)
LTC4332 -> the remote SPI devices need to be configure (to mode=1 for the AS5047D). This is done locally with SSC (runs in mode 0), see table 3, register map, page 16.
isoSPI (twisted pairs)
__CS_Bot
7-bit I2C address: 0x3E Speed set to 100kHz clk
/!\ Le Pico8 vers Donut est un câble croisé de manière à être plat (équivalent d'un flex) /!\
__CS_Mid
__CS_Top
